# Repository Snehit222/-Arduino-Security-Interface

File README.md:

# -Arduino-Security-Interface
A Arduino pcb that is for a smart house system simulator

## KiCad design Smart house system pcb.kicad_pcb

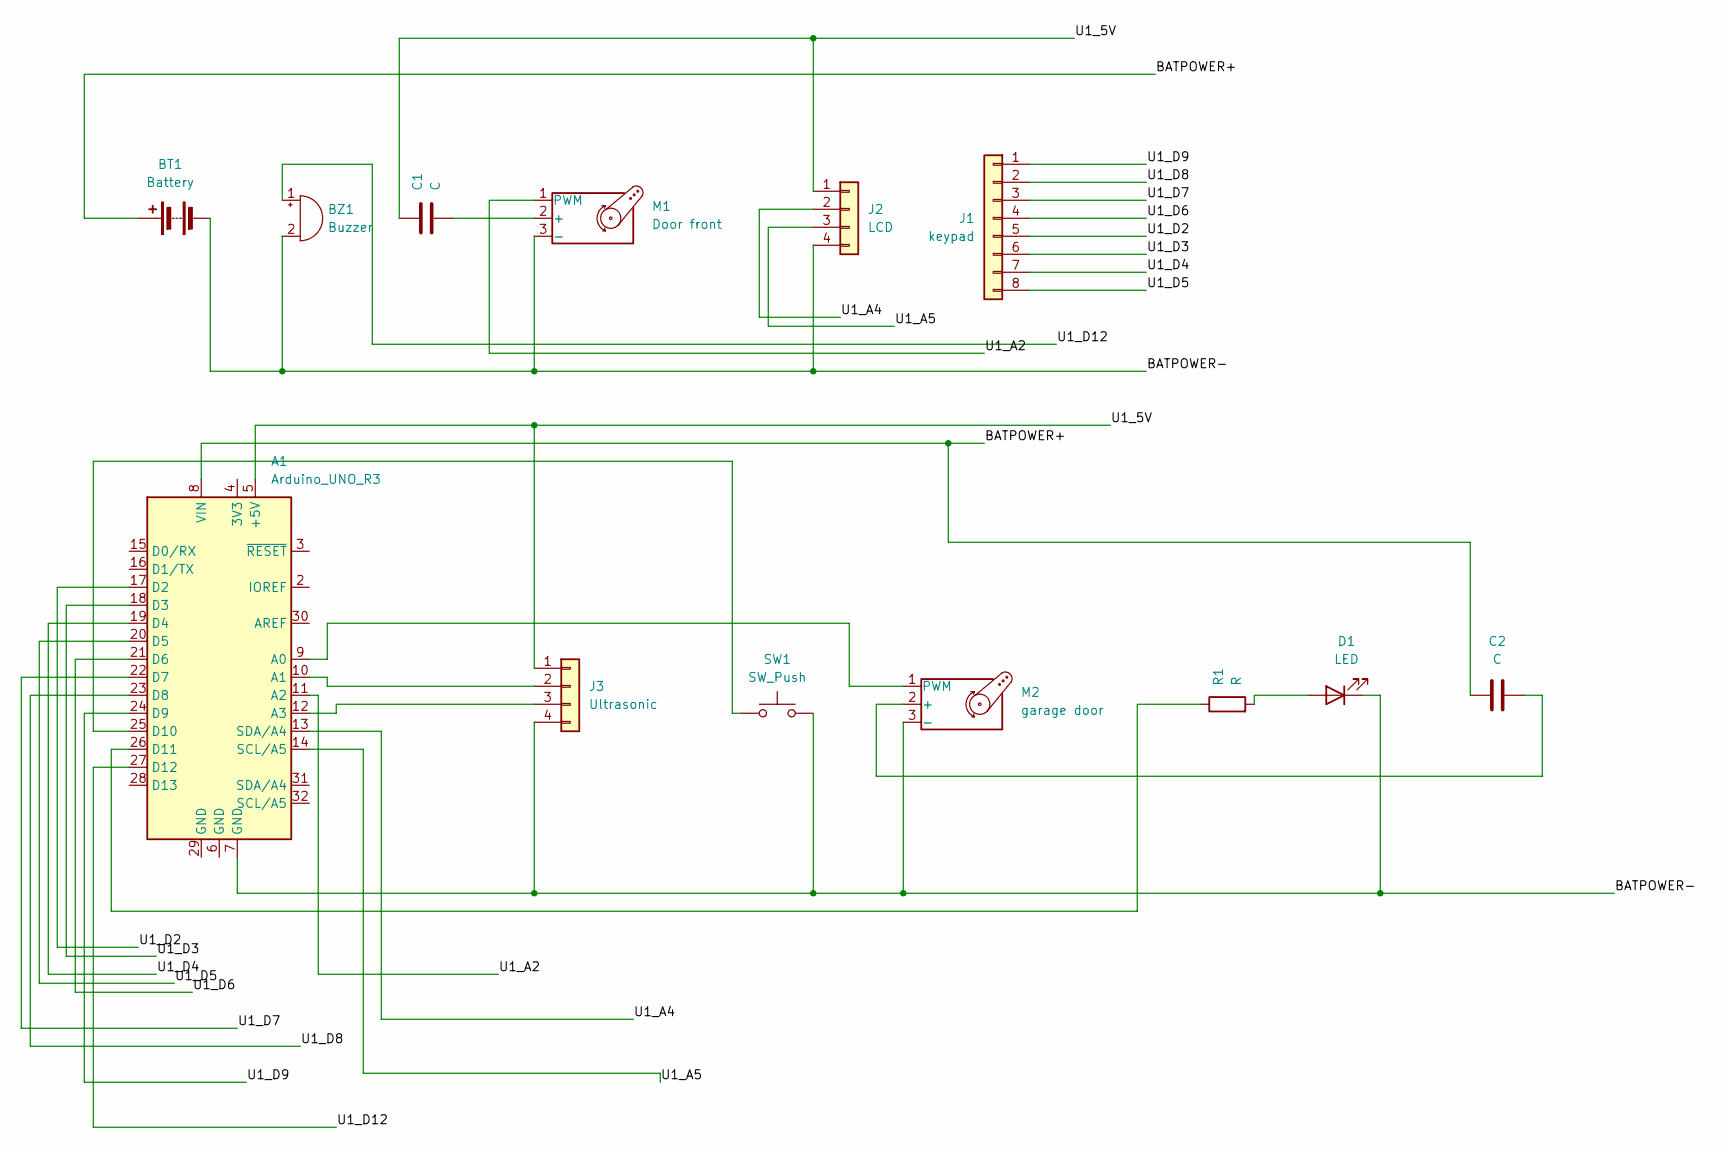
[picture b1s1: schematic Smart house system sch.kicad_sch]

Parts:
A1: Arduino_UNO_R3
BT1: Battery; BatteryHolder_Keystone_2479_3xAAA
BZ1: Buzzer; Buzzer_D14mm_H7mm_P10mm
C1, C2: C; C_0805_2012Metric
D1: LED; LED_0805_2012Metric
J1: keypad; PinHeader_1x08_P2.54mm_Vertical
J2: LCD; FanPinHeader_1x04_P2.54mm_Vertical
J3: Ultrasonic; FanPinHeader_1x04_P2.54mm_Vertical
M1: Door front; FanPinHeader_1x03_P2.54mm_Vertical
M2: garage door; FanPinHeader_1x03_P2.54mm_Vertical
R1: R; R_0805_2012Metric
SW1: SW_Push; SW_PUSH_6mm

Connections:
/BATPOWER+: A1.8 (VIN), BT1.1 (+), C2.1
/BATPOWER-: A1.7 (GND), BT1.2 (-), BZ1.2 (-), D1.1 (K), J2.4, J3.4, M1.3 (-), M2.3 (-), SW1.2
/U1_5V: A1.5 (+5V), C1.1, J2.1, J3.1
/U1_A2: A1.11 (A2), M1.1 (PWM)
/U1_A4: A1.13 (SDA/A4), J2.2
/U1_A5: A1.14 (SCL/A5), J2.3
/U1_D2: A1.17 (D2), J1.5
/U1_D3: A1.18 (D3), J1.6
/U1_D4: A1.19 (D4), J1.7
/U1_D5: A1.20 (D5), J1.8
/U1_D6: A1.21 (D6), J1.4
/U1_D7: A1.22 (D7), J1.3
/U1_D8: A1.23 (D8), J1.2
/U1_D9: A1.24 (D9), J1.1
/U1_D12: A1.27 (D12), BZ1.1 (+)
unnamed: A1.9 (A0), M2.1 (PWM)
unnamed: A1.10 (A1), J3.2
unnamed: A1.12 (A3), J3.3
unnamed: A1.25 (D10), SW1.1
unnamed: A1.26 (D11), R1.1
unnamed: D1.2 (A), R1.2
unnamed: C1.2, M1.2 (+)
unnamed: C2.2, M2.2 (+)

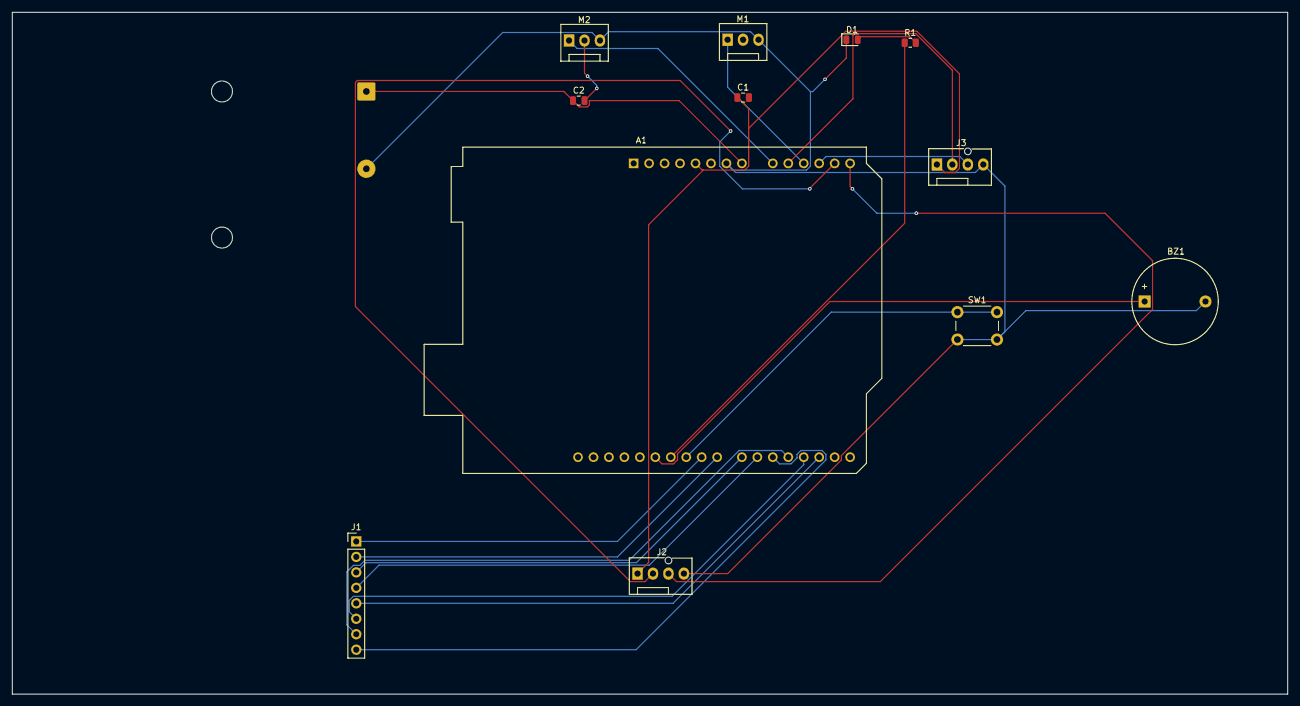
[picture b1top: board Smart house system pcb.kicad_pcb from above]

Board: 2 copper layers, 209.5 x 112.0 mm, 13 parts (1 on the bottom side), 23 nets.
